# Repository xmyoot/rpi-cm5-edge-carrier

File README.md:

# CM5 Edge-Audio Carrier

A compact **Raspberry Pi Compute Module 5 carrier board** for an always-on edge-AI audio
appliance. It is designed in **KiCad 10**, impedance-controlled on a **4-layer JLCPCB stack**,
and fully routed with **0 DRC errors, 0 unconnected items and 0 schematic-parity issues**.

| | |
|---|---|
| **Compute** | Raspberry Pi CM5 (BCM2712, 4x Cortex-A76) on 2x Hirose DF40 100-pin receptacles |
| **Board** | 100 x 85 mm, 4 layers, 1.6 mm, JLC04161H-3313 stackup, ENIG |
| **Power in** | USB-C PD sink (CH224K) negotiates **12 V / 3 A**, with a TVS-clamped input |
| **Rails** | 5 V / 5 A synchronous buck (TPS565208); 3.3 V / 2 A buck for NVMe (AP3441), gated by the CM5 |
| **Storage** | M.2 Key-M socket, NVMe 2230/2242, PCIe x1 (Gen2, Gen3 capable) |
| **USB** | 1x USB 3.0 (5 Gb/s) + 1x USB 2.0 in a stacked Type-A with a 1.5 A current-limited VBUS |
| **Network** | Gigabit Ethernet RJ45 MagJack with an ESD array on every MDI pair |
| **Audio link** | 2x6 header to a 6-mic XVF3800 array: I2S + I2C control + reset/IRQ |
| **Other I/O** | USB-C service port (rpiboot / gadget), debug UART, barcode-scanner UART, Qwiic I2C, PWM fan, status LEDs, power and boot buttons |
| **Parts** | 90 footprints, 231 nets, 474 vias, 3.4 m of copper |

---

## 1. System architecture

The board started from the requirements of a Jetson Orin NX carrier for emergency-vehicle
audio. It keeps the same functional set (PD power path, NVMe, high-speed USB, GbE, I2S
mic-array link, UART/I2C management, ESD on external ports), but runs on a Raspberry Pi
CM5. Every peripheral maps to a native CM5 interface, so the carrier needs **no bridge ICs**:

| Function | CM5 interface | Carrier hardware |
|---|---|---|
| NVMe SSD | PCIe x1 (+REFCLK, PERST#, CLKREQ#, WAKE#) | M.2 Key-M socket + switched 3.3 V rail (`PCIE_PWR_EN`) |
| USB 3.0 port | USB3-0 SuperSpeed + D+/D- | Stacked Type-A (upper port), AP22653 VBUS switch |
| USB 2.0 port | USB3-1 D+/D- | Stacked Type-A (lower port) |
| Flashing / gadget | USB2 OTG | USB-C service port, USBLC6-2 ESD, 5.1k Rd |
| Ethernet | On-module BCM54210 PHY, MDI x4 | TRJG0926HENL MagJack + 2x TPD4EUSB30 |
| Mic array | PCM/I2S on GPIO18-21, I2C1, GPIO26/27 | 2x6 shrouded header, 33 ohm source termination |
| Scanner / console | UART2 / UART0 | JST-SH 4-pin / 1x3 header |

## 2. Schematic

Five hierarchical sheets ([PDF](docs/CM5_Edge_Carrier_schematic.pdf)): Root (block diagram and
notes), Power, Compute Module, High-Speed IO, and Peripheral IO.

| Power | High-speed IO |
|---|---|
|  |  |

Key circuit decisions:

* **PD with UVLO interlock.** The CH224K requests 12 V (`CFG1` = 24k). The buck's EN divider
  (100k/15k) sets the turn-on point near 9 V. If a charger can only give 5 V, the 5 V rail stays
  off instead of browning out the CM5.
* **Buck sizing.** V<sub>out</sub> = 0.76 V x (1 + 56k/10k) = 5.02 V. The worst-case load is
  CM5 3 A + USB 1.5 A + fan 0.2 A = 4.7 A, under the TPS565208's 5 A rating.
  The NVMe rail uses V<sub>out</sub> = 0.6 V x (1 + 10k/2.2k) = 3.33 V and has a 4.7 nF feed-forward cap.
* **The NVMe rail is gated by the SoC** (`PCIE_PWR_EN` with a 100k pull-down). The SSD stays
  unpowered until the bootloader wants it, as on the Raspberry Pi reference design.
* **The ESD strategy follows the threat.** SMAJ15A on the PD input, TPD4EUSB30 on all four GbE
  pairs, and USBLC6-2 on the service port. The USB-A ports follow the Raspberry Pi CM5 IO
  reference, which has no array on the 5 Gb/s pair, so that pair stays stub- and via-free.

## 3. PCB layout

| Top copper | Bottom copper |
|---|---|
|  |  |

**Floorplan.** The CM5 is rotated so its high-speed connector (PCIe/USB) faces the front edge.
The USB 3.0 jack, the service USB-C and the M.2 socket sit directly at those pins. The Ethernet
pins face the rear edge, where the MagJack is. Power enters at the top-left and the M.2 buck
sits next to the socket. Nothing is placed under the module.

**Stackup and impedance.** JLC04161H-3313: L1 signal / **L2 solid GND** / L3 power (+5 V plane
with a +3V3_M2 island) / L4 signal. The widths below were solved with the
[KiCadRoutingTools](https://github.com/drandyhaas/KiCadRoutingTools) microstrip models for L1
over 0.0994 mm 3313 prepreg (εr 4.1):

| Class | Target | Width / gap | Calculated |
|---|---|---|---|
| PCIe TX/RX/REFCLK | 85 ohm diff | 0.20 / 0.15 mm | 85.6 ohm |
| USB 3.0 SS, USB 2.0 | 90 ohm diff | 0.18 / 0.15 mm | 90.8 ohm |
| 1000BASE-T MDI | 100 ohm diff | 0.16 / 0.18 mm | 100.0 ohm |

**High-speed results**, measured from the routed copper by `scripts/si_report.py`:

| Pair | Length P / N (mm) | Intra-pair skew | Vias | Layer |
|---|---|---|---|---|
| PCIe TX | 52.33 / 52.33 | 0.01 mm | 0 | L1 only |
| PCIe RX | 99.69 / 99.69 | 0.00 mm | 0 | L1 only |
| PCIe REFCLK | 50.02 / 49.76 | 0.26 mm | 4 | L1/L4 (must cross TX/RX) |
| USB 3.0 SSTX | 11.37 / 11.33 | 0.04 mm | 0 | L1 only |
| USB 3.0 SSRX | 9.20 / 9.20 | 0.00 mm | 0 | L1 only |
| USB-A1 D+/D- | 10.66 / 11.24 | 0.58 mm | 0 | L1 only |
| USB-A2 D+/D- | 55.01 / 55.07 | 0.06 mm | 4 | L1/L4 |

The 5 Gb/s and PCIe data pairs stay on L1, over an unbroken L2 ground, with no layer changes,
and their P/N lengths are matched with meanders. The Ethernet pairs carry short T-stubs to their
ESD clamps. At 125 MBd those stubs are electrically negligible.

**Power stage.** Both bucks are laid out by hand on top-layer copper pours: input cap, then IC,
then inductor, then output caps, in a tight loop with stitched returns. The CM5's 0.4 mm-pitch
DF40 pads use a custom staggered escape fanout (0.4/0.2 mm vias, 3 levels) that keeps the
design on JLC's standard process. Outer GND pours are stitched to L2 on a 4 mm grid
(about 210 vias).

| Rear (RJ45, mic header) | Top |
|---|---|
|  |  |

## 4. Engineering trade-offs (documented, deliberate)

1. **CM5 instead of Jetson Orin NX.** The same functions at a fraction of the power and cost. NVMe
   runs at PCIe Gen2/3 x1 instead of Gen3 x4.
2. **Lower USB-A port is USB 2.0.** The far contact row of a stacked USB3 jack is only reachable
   by threading pairs between the near-row pins. One clean 5 Gb/s port covers the 5G-modem use
   case, so the CM5's second SuperSpeed lane is left unconnected.
3. **No battery charger.** The input path is PD to buck. A UPS or battery stage would be a
   daughterboard.
4. **The CM5 CC1/CC2 pins are left open.** PD is negotiated by the CH224K, so set
   `usb_max_current_enable=1` in `config.txt` to get full USB current.
5. **LCSC codes** are filled in where verified against the LCSC catalogue (October 2026). The
   remaining lines are ordered by manufacturer part number.

## 5. Fabrication package (`fab/`)

* `CM5_Edge_Carrier_gerbers.zip`: Gerber X2 for 4 copper layers, mask, paste, silk, outline, and Excellon drills
* `CM5_Edge_Carrier_BOM_JLC.csv` / `CM5_Edge_Carrier_CPL_JLC.csv`: JLCPCB SMT assembly format
* `CM5_Edge_Carrier.step`: full 3D assembly, including the CM5 module
* `CM5_Edge_Carrier_schematic.pdf`, `CM5_Edge_Carrier_top_assembly.pdf`

Order notes: JLC04161H-3313 impedance control, 1.6 mm, ENIG, minimum via 0.4/0.2 mm, and
minimum track/space 0.1/0.1 mm. Everything is on JLC's standard multilayer tier.

## 6. Reproducible design flow (`scripts/`)

The schematic, board, routing and fab outputs are generated from one design database, so
they cannot drift apart:

```
design.py          parts, values, nets, schematic placement     (single source of truth)
gen_sch.py         -> hierarchical KiCad schematic with wires, labels and frames
check_netlist.py   KiCad-exported netlist == design.py           (catches any wiring error)
gen_pcb.py         -> board: floorplan, stackup, netclasses, power-stage pours
fanout_cm5.py      staggered DF40 escape vias
route_chain.sh     KiCadRoutingTools: diff pairs (85/90/100 ohm, length-matched) -> general routing
finish_pcb.py / stitch_gnd.py / silk_cleanup.py   zone fill, GND stitching, silkscreen placement
si_report.py       length / skew / via report
make_outputs.sh    Gerbers, drills, JLC BOM/CPL, STEP, PDFs, renders
```

`scripts/build_all.sh` runs the whole flow, from schematic to a DRC-clean routed board, in
about 4 minutes. Requirements: KiCad 10 (its bundled Python runs the `pcbnew` scripts; the
paths are set at the top of each shell script), plus
`git clone https://github.com/drandyhaas/KiCadRoutingTools ref/KiCadRoutingTools` followed by
`python3 ref/KiCadRoutingTools/build_router.py`.

## 7. Repository layout

```
hardware/   KiCad 10 project (schematic, PCB, project rules, project symbol/footprint/3D library)
fab/        manufacturing outputs
docs/       renders, layer plots, schematic PDF
scripts/    generators and build flow
```

## Credits and licenses

* The CM5 symbol, DF40 footprint, magjack, stacked USB3 and M.2 footprints and their 3D models
  are adapted from the **Raspberry Pi CM5 IO Board** KiCad design files (Raspberry Pi Ltd,
  [design-files licence](https://pip.raspberrypi.com)). The CM5 STEP model is © Raspberry Pi Ltd.
* Approach inspired by Shawn Hymel's
  [CM4 carrier template](https://github.com/ShawnHymel/rpi-cm4-carrier-template) and the
  [MakerForge CM5 carrier basics](https://www.makerforge.tech/posts/cm5-carrier-basics/).
* Routing by [KiCadRoutingTools](https://github.com/drandyhaas/KiCadRoutingTools) (MIT).
  Design review by [kicad-happy](https://github.com/aklofas/kicad-happy).
* This design: hardware files are CC BY 4.0, scripts are MIT. Hector Jimenez, 2026.

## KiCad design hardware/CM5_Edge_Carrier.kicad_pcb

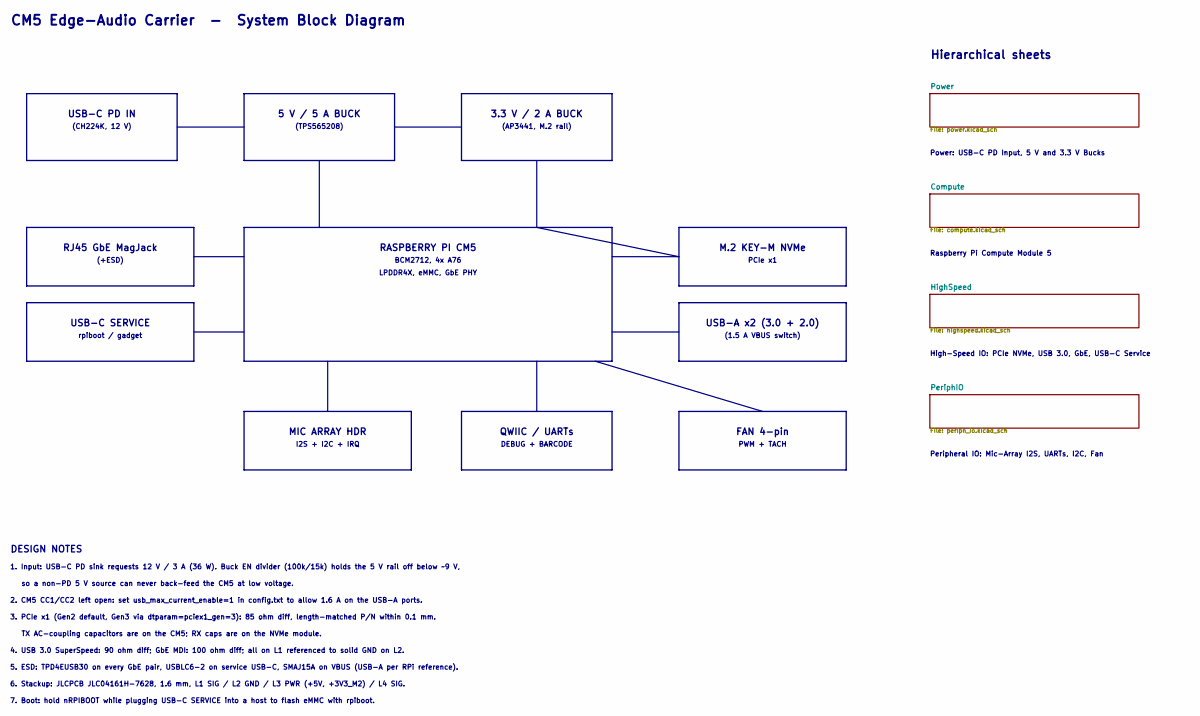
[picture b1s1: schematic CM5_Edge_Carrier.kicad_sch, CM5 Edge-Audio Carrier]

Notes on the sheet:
USB-C PD IN
(CH224K, 12 V)
5 V / 5 A BUCK
(TPS565208)
3.3 V / 2 A BUCK
(AP3441, M.2 rail)
RASPBERRY PI CM5
BCM2712, 4x A76
LPDDR4X, eMMC, GbE PHY
M.2 KEY-M NVMe
PCIe x1
USB-A x2 (3.0 + 2.0)
(1.5 A VBUS switch)
RJ45 GbE MagJack
(+ESD)
USB-C SERVICE
rpiboot / gadget
MIC ARRAY HDR
I2S + I2C + IRQ
QWIIC / UARTs
DEBUG + BARCODE
FAN 4-pin
PWM + TACH
CM5 Edge-Audio Carrier - System Block Diagram
DESIGN NOTES
1. Input: USB-C PD sink requests 12 V / 3 A (36 W). Buck EN divider (100k/15k) holds the 5 V rail off below ~9 V,
so a non-PD 5 V source can never back-feed the CM5 at low voltage.
2. CM5 CC1/CC2 left open: set usb_max_current_enable=1 in config.txt to allow 1.6 A on the USB-A ports.
3. PCIe x1 (Gen2 default, Gen3 via dtparam=pciex1_gen=3): 85 ohm diff, length-matched P/N within 0.1 mm.
TX AC-coupling capacitors are on the CM5; RX caps are on the NVMe module.
4. USB 3.0 SuperSpeed: 90 ohm diff; GbE MDI: 100 ohm diff; all on L1 referenced to solid GND on L2.
5. ESD: TPD4EUSB30 on every GbE pair, USBLC6-2 on service USB-C, SMAJ15A on VBUS (USB-A per RPi reference).
6. Stackup: JLCPCB JLC04161H-7628, 1.6 mm, L1 SIG / L2 GND / L3 PWR (+5V, +3V3_M2) / L4 SIG.
7. Boot: hold nRPIBOOT while plugging USB-C SERVICE into a host to flash eMMC with rpiboot.
Hierarchical sheets
Power: USB-C PD Input, 5 V and 3.3 V Bucks
Raspberry Pi Compute Module 5
High-Speed IO: PCIe NVMe, USB 3.0, GbE, USB-C Service
Peripheral IO: Mic-Array I2S, UARTs, I2C, Fan

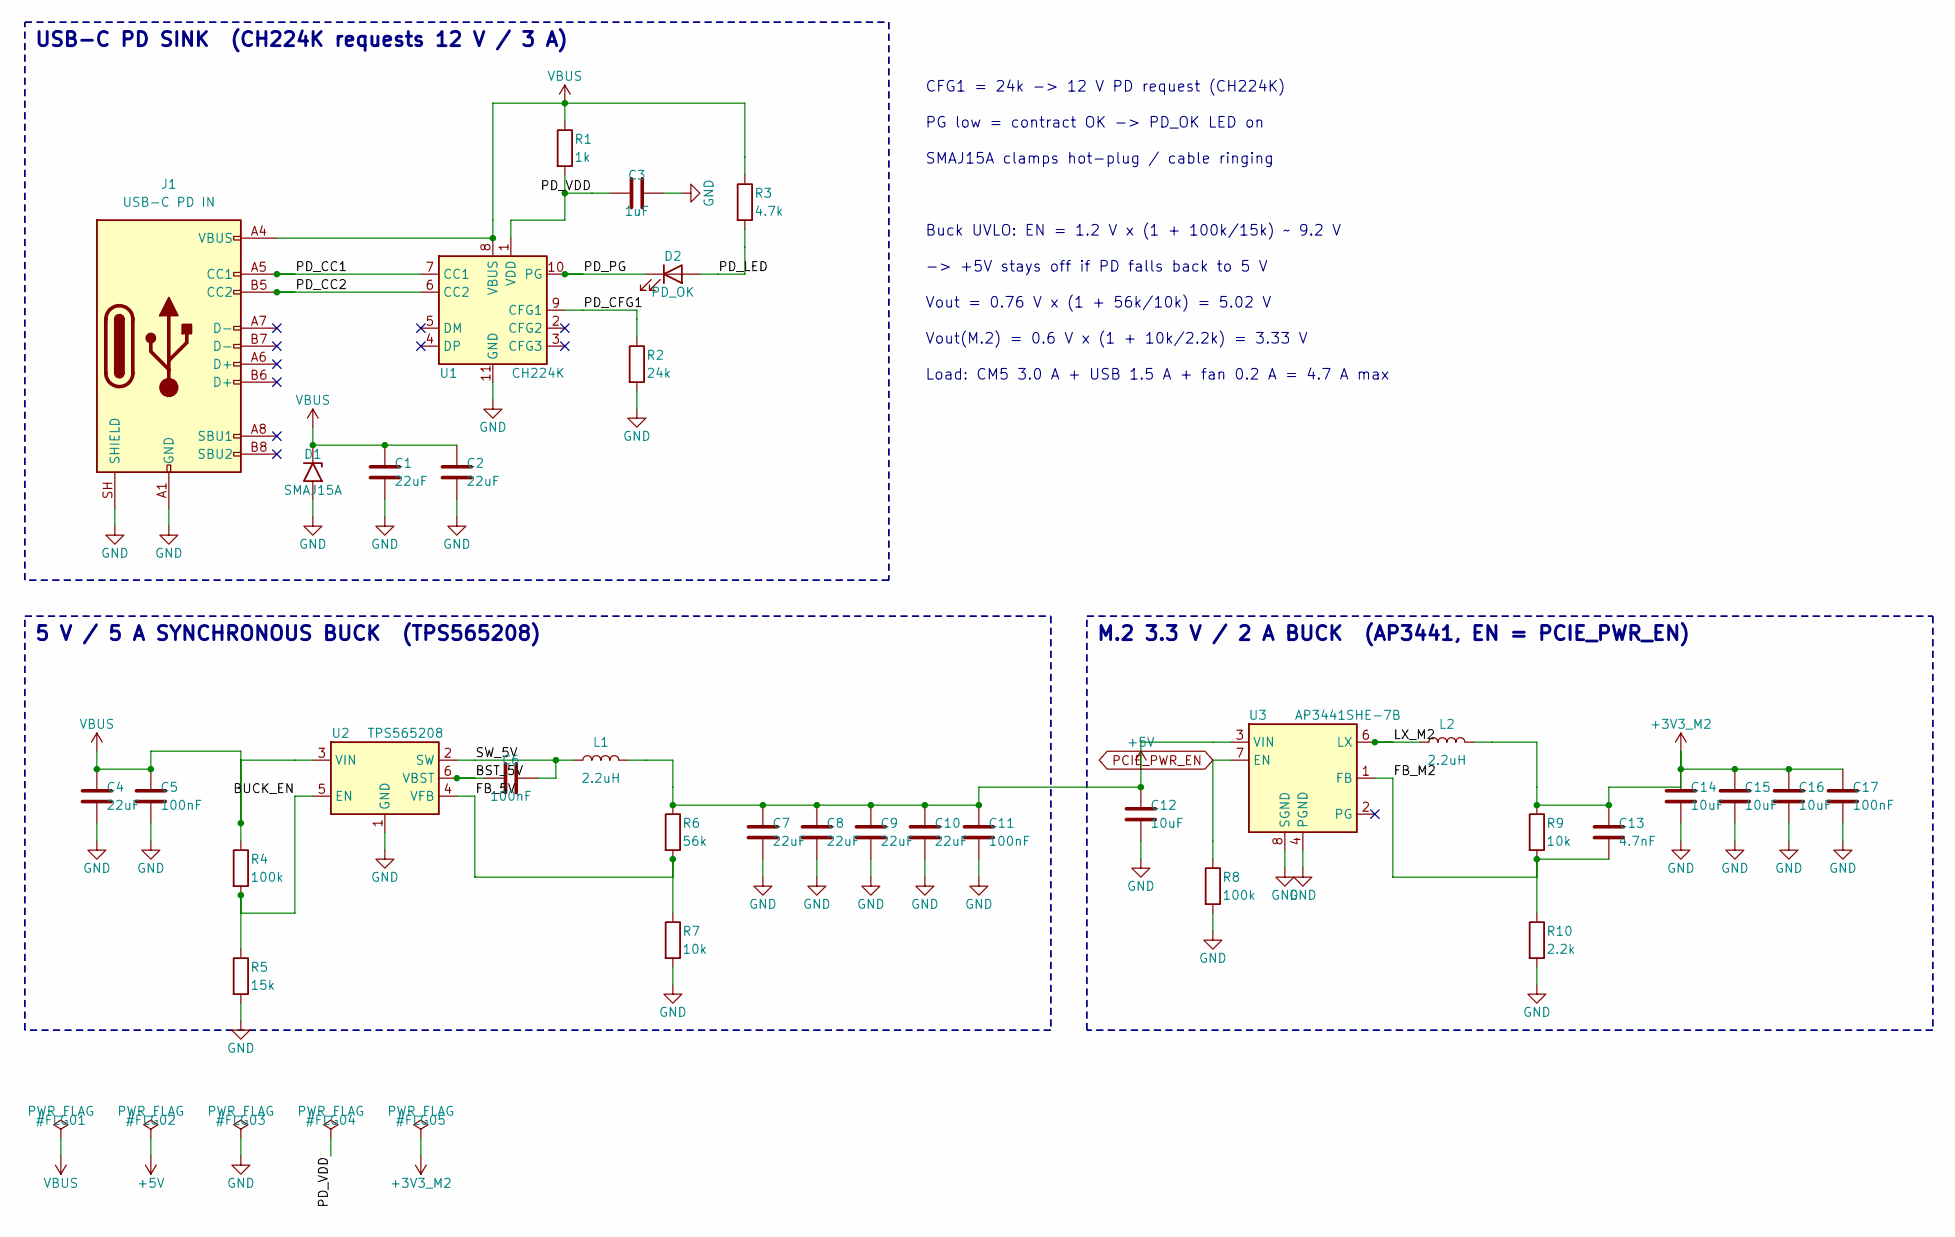
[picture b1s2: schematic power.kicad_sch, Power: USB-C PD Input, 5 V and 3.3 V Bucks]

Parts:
C1, C2, C4: 22uF; C_1206_3216Metric; Voltage 25V; LCSC C12891
C3: 1uF; C_0402_1005Metric; Voltage 16V; LCSC C52923
C5, C6, C11, C17: 100nF; C_0402_1005Metric; Voltage 16V; LCSC C1525
C7, C8, C9, C10: 22uF; C_0805_2012Metric; Voltage 10V; LCSC C45783
C12, C14, C15, C16: 10uF; C_0805_2012Metric; Voltage 10V; LCSC C15850
C13: 4.7nF; C_0402_1005Metric; Voltage 16V; LCSC C1538
D1: SMAJ15A; D_SMA; MPN Littelfuse SMAJ15A
D2: PD_OK; LED_0603_1608Metric; LCSC C72043
J1: USB-C PD IN; USB_C_Receptacle_GCT_USB4105-xx-A_16P_TopMnt_Horizontal; MPN GCT USB4105-GF-A; LCSC C3020560
L1: 2.2uH; L_Sunlord_MWSA0603S; Rating 2.2uH 10A; MPN Sunlord MWSA0603S-2R2MT
L2: 2.2uH; L_Bourns_SRP5030T; Rating 2.2uH 6.5A; MPN Bourns SRP5030T-2R2M
R1: 1k; R_0402_1005Metric; Tolerance 1%; LCSC C11702
R2: 24k; R_0402_1005Metric; Tolerance 1%
R3: 4.7k; R_0402_1005Metric; Tolerance 1%; LCSC C25900
R4, R8: 100k; R_0402_1005Metric; Tolerance 1%; LCSC C25741
R5: 15k; R_0402_1005Metric; Tolerance 1%; LCSC C25756
R6: 56k; R_0402_1005Metric; Tolerance 1%; LCSC C25796
R7, R9: 10k; R_0402_1005Metric; Tolerance 1%; LCSC C25744
R10: 2.2k; R_0402_1005Metric; Tolerance 1%; LCSC C25879
U1: CH224K; SSOP-10-1EP_3.9x4.9mm_P1mm_EP2.1x3.3mm; MPN WCH CH224K; LCSC C970725
U2: TPS565208; SOT-23-6; MPN TI TPS565208DDCR
U3: AP3441SHE-7B; DFN-8-1EP_2x2mm_P0.5mm_EP0.9x1.7mm; MPN Diodes AP3441SHE-7B

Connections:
+3V3_M2: C13.1, C14.1, C15.1, C16.1, C17.1, L2.2, R9.1; also elsewhere on the board
+5V: C7.1, C8.1, C9.1, C10.1, C11.1, C12.1, L1.2, R6.1, U3.3 (VIN); also elsewhere on the board
/Power/BST_5V: C6.1, U2.6 (VBST)
/Power/BUCK_EN: R4.2, R5.1, U2.5 (EN)
/Power/FB_5V: R6.2, R7.1, U2.4 (VFB)
/Power/FB_M2: C13.2, R9.2, R10.1, U3.1 (FB)
/Power/LX_M2: L2.1, U3.6 (LX)
/Power/PD_CC1: J1.A5 (CC1), U1.7 (CC1)
/Power/PD_CC2: J1.B5 (CC2), U1.6 (CC2)
/Power/PD_CFG1: R2.1, U1.9 (CFG1)
/Power/PD_LED: D2.2 (A), R3.2
/Power/PD_PG: D2.1 (K), U1.10 (PG)
/Power/PD_VDD: C3.1, R1.2, U1.1 (VDD)
/Power/SW_5V: C6.2, L1.1, U2.2 (SW)
GND: C1.2, C2.2, C3.2, C4.2, C5.2, C7.2, C8.2, C9.2, C10.2, C11.2, C12.2, C14.2, C15.2, C16.2, C17.2, D1.2 (A2), J1.A1 (GND), J1.A12 (GND), J1.B1 (GND), J1.B12 (GND), J1.SH (SHIELD), R2.2, R5.2, R7.2, R8.2, R10.2, U1.11 (GND), U2.1 (GND), U3.4 (PGND), U3.8 (SGND), U3.9 (SGND); also elsewhere on the board
PCIE_PWR_EN: R8.1, U3.7 (EN); also elsewhere on the board
VBUS: C1.1, C2.1, C4.1, C5.1, D1.1 (A1), J1.A4 (VBUS), J1.A9 (VBUS), J1.B4 (VBUS), J1.B9 (VBUS), R1.1, R3.1, R4.1, U1.8 (VBUS), U2.3 (VIN)

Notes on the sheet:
USB-C PD SINK (CH224K requests 12 V / 3 A)
5 V / 5 A SYNCHRONOUS BUCK (TPS565208)
M.2 3.3 V / 2 A BUCK (AP3441, EN = PCIE_PWR_EN)
CFG1 = 24k -> 12 V PD request (CH224K)
PG low = contract OK -> PD_OK LED on
SMAJ15A clamps hot-plug / cable ringing
Buck UVLO: EN = 1.2 V x (1 + 100k/15k) ~ 9.2 V
-> +5V stays off if PD falls back to 5 V
Vout = 0.76 V x (1 + 56k/10k) = 5.02 V
Vout(M.2) = 0.6 V x (1 + 10k/2.2k) = 3.33 V
Load: CM5 3.0 A + USB 1.5 A + fan 0.2 A = 4.7 A max

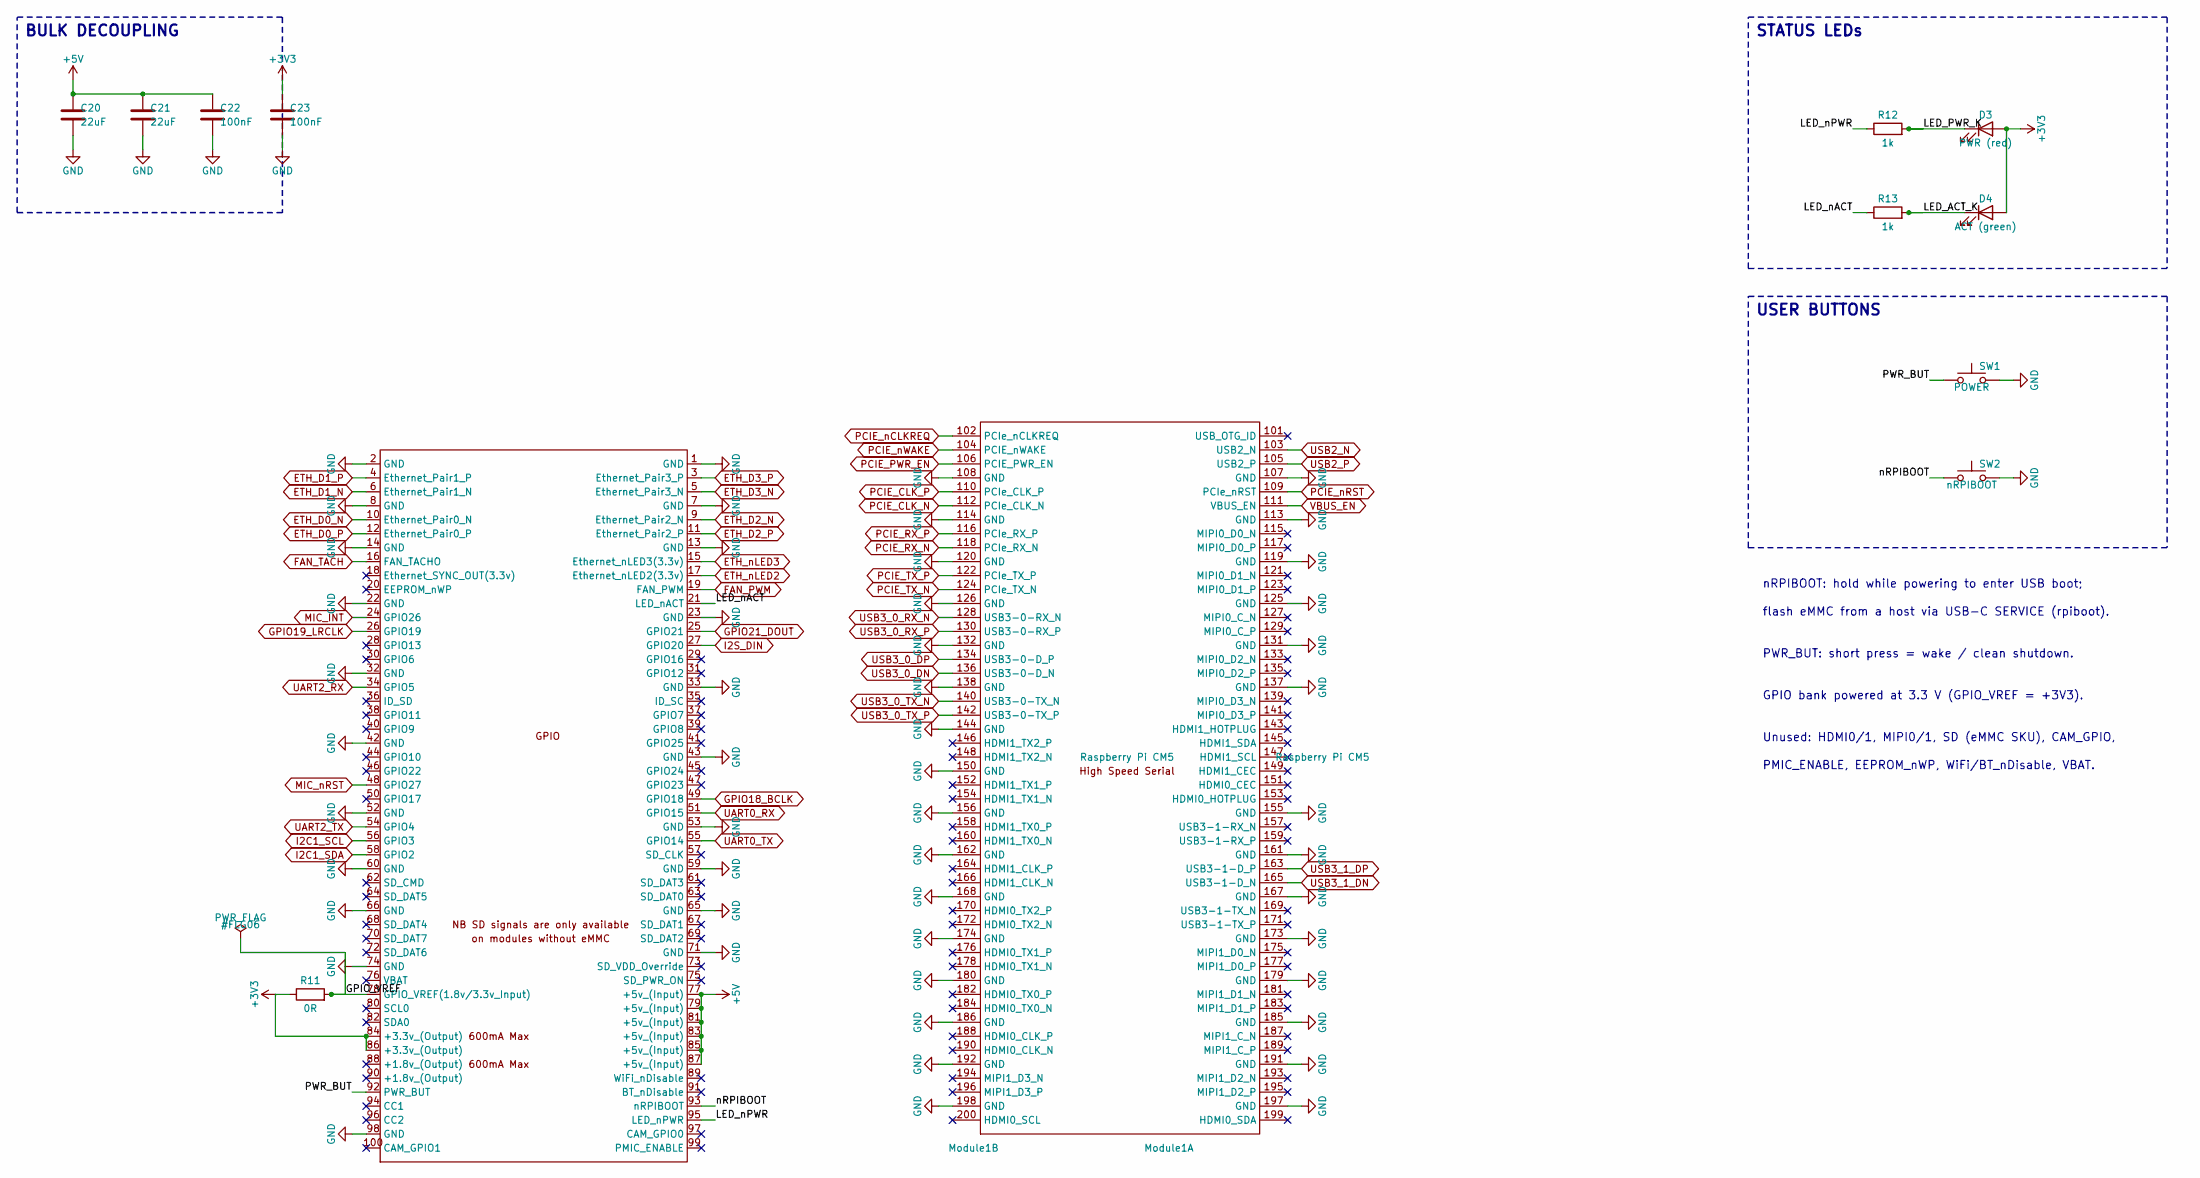
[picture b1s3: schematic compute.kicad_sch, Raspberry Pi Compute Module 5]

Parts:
C20, C21: 22uF; C_0805_2012Metric; Voltage 10V; LCSC C45783
C22, C23: 100nF; C_0402_1005Metric; Voltage 16V; LCSC C1525
D3: PWR (red); LED_0603_1608Metric; LCSC C2286
D4: ACT (green); LED_0603_1608Metric; LCSC C72043
Module1: Raspberry Pi CM5; RPi_CM5_DF40; MPN Raspberry Pi CM5 + 2x Hirose DF40C-100D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; LCSC C597931 (x2)
R11: 0R; R_0402_1005Metric; Tolerance 1%; LCSC C17168
R12, R13: 1k; R_0402_1005Metric; Tolerance 1%; LCSC C11702
SW1: POWER; SW_SPST_B3U-1000P; MPN Omron B3U-1000P; LCSC C231329
SW2: nRPIBOOT; SW_SPST_B3U-1000P; MPN Omron B3U-1000P; LCSC C231329

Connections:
+3V3: C23.1, D3.2 (A), D4.2 (A), Module1.84 (+3.3v_(Output)), Module1.86 (+3.3v_(Output)), R11.1; also elsewhere on the board
+5V: C20.1, C21.1, C22.1, Module1.77 (+5v_(Input)), Module1.79 (+5v_(Input)), Module1.81 (+5v_(Input)), Module1.83 (+5v_(Input)), Module1.85 (+5v_(Input)), Module1.87 (+5v_(Input)); also elsewhere on the board
/Compute/GPIO_VREF: Module1.78 (GPIO_VREF(1.8v/3.3v_Input)), R11.2
/Compute/LED_ACT_K: D4.1 (K), R13.2
/Compute/LED_PWR_K: D3.1 (K), R12.2
/Compute/LED_nACT: Module1.21 (LED_nACT), R13.1
/Compute/LED_nPWR: Module1.95 (LED_nPWR), R12.1
/Compute/PWR_BUT: Module1.92 (PWR_BUT), SW1.1
/Compute/nRPIBOOT: Module1.93 (nRPIBOOT), SW2.1
ETH_D0_N: Module1.10 (Ethernet_Pair0_N); also elsewhere on the board
ETH_D0_P: Module1.12 (Ethernet_Pair0_P); also elsewhere on the board
ETH_D1_N: Module1.6 (Ethernet_Pair1_N); also elsewhere on the board
ETH_D1_P: Module1.4 (Ethernet_Pair1_P); also elsewhere on the board
ETH_D2_N: Module1.9 (Ethernet_Pair2_N); also elsewhere on the board
ETH_D2_P: Module1.11 (Ethernet_Pair2_P); also elsewhere on the board
ETH_D3_N: Module1.5 (Ethernet_Pair3_N); also elsewhere on the board
ETH_D3_P: Module1.3 (Ethernet_Pair3_P); also elsewhere on the board
ETH_nLED2: Module1.17 (Ethernet_nLED2(3.3v)); also elsewhere on the board
ETH_nLED3: Module1.15 (Ethernet_nLED3(3.3v)); also elsewhere on the board
FAN_PWM: Module1.19 (FAN_PWM); also elsewhere on the board
FAN_TACH: Module1.16 (FAN_TACHO); also elsewhere on the board
GND: C20.2, C21.2, C22.2, C23.2, Module1.1 (GND), Module1.2 (GND), Module1.7 (GND), Module1.8 (GND), Module1.13 (GND), Module1.14 (GND), Module1.22 (GND), Module1.23 (GND), Module1.32 (GND), Module1.33 (GND), Module1.42 (GND), Module1.43 (GND), Module1.52 (GND), Module1.53 (GND), Module1.59 (GND), Module1.60 (GND), Module1.65 (GND), Module1.66 (GND), Module1.71 (GND), Module1.74 (GND), Module1.98 (GND), Module1.107 (GND), Module1.108 (GND), Module1.113 (GND), Module1.114 (GND), Module1.119 (GND), Module1.120 (GND), Module1.125 (GND), Module1.126 (GND), Module1.131 (GND), Module1.132 (GND), Module1.137 (GND), Module1.138 (GND), Module1.144 (GND), Module1.150 (GND), Module1.155 (GND), Module1.156 (GND), Module1.161 (GND), Module1.162 (GND), Module1.167 (GND), Module1.168 (GND), Module1.173 (GND), Module1.174 (GND), Module1.179 (GND), Module1.180 (GND), Module1.185 (GND), Module1.186 (GND), Module1.191 (GND), Module1.192 (GND), Module1.197 (GND), Module1.198 (GND), SW1.2, SW2.2; also elsewhere on the board
GPIO18_BCLK: Module1.49 (GPIO18); also elsewhere on the board
GPIO19_LRCLK: Module1.26 (GPIO19); also elsewhere on the board
GPIO21_DOUT: Module1.25 (GPIO21); also elsewhere on the board
I2C1_SCL: Module1.56 (GPIO3); also elsewhere on the board
I2C1_SDA: Module1.58 (GPIO2); also elsewhere on the board
I2S_DIN: Module1.27 (GPIO20); also elsewhere on the board
MIC_INT: Module1.24 (GPIO26); also elsewhere on the board
MIC_nRST: Module1.48 (GPIO27); also elsewhere on the board
PCIE_CLK_N: Module1.112 (PCIe_CLK_N); also elsewhere on the board
PCIE_CLK_P: Module1.110 (PCIe_CLK_P); also elsewhere on the board
PCIE_PWR_EN: Module1.106 (PCIE_PWR_EN); also elsewhere on the board
PCIE_RX_N: Module1.118 (PCIe_RX_N); also elsewhere on the board
PCIE_RX_P: Module1.116 (PCIe_RX_P); also elsewhere on the board
PCIE_TX_N: Module1.124 (PCIe_TX_N); also elsewhere on the board
PCIE_TX_P: Module1.122 (PCIe_TX_P); also elsewhere on the board
PCIE_nCLKREQ: Module1.102 (PCIe_nCLKREQ); also elsewhere on the board
PCIE_nRST: Module1.109 (PCIe_nRST); also elsewhere on the board
PCIE_nWAKE: Module1.104 (PCIE_nWAKE); also elsewhere on the board
UART0_RX: Module1.51 (GPIO15); also elsewhere on the board
UART0_TX: Module1.55 (GPIO14); also elsewhere on the board
UART2_RX: Module1.34 (GPIO5); also elsewhere on the board
UART2_TX: Module1.54 (GPIO4); also elsewhere on the board
USB2_N: Module1.103 (USB2_N); also elsewhere on the board
USB2_P: Module1.105 (USB2_P); also elsewhere on the board
USB3_0_DN: Module1.136 (USB3-0-D_N); also elsewhere on the board
USB3_0_DP: Module1.134 (USB3-0-D_P); also elsewhere on the board
USB3_0_RX_N: Module1.128 (USB3-0-RX_N); also elsewhere on the board
USB3_0_RX_P: Module1.130 (USB3-0-RX_P); also elsewhere on the board
USB3_0_TX_N: Module1.140 (USB3-0-TX_N); also elsewhere on the board
USB3_0_TX_P: Module1.142 (USB3-0-TX_P); also elsewhere on the board
USB3_1_DN: Module1.165 (USB3-1-D_N); also elsewhere on the board
USB3_1_DP: Module1.163 (USB3-1-D_P); also elsewhere on the board
VBUS_EN: Module1.111 (VBUS_EN); also elsewhere on the board

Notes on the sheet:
BULK DECOUPLING
STATUS LEDs
USER BUTTONS
nRPIBOOT: hold while powering to enter USB boot;
flash eMMC from a host via USB-C SERVICE (rpiboot).
PWR_BUT: short press = wake / clean shutdown.
GPIO bank powered at 3.3 V (GPIO_VREF = +3V3).
Unused: HDMI0/1, MIPI0/1, SD (eMMC SKU), CAM_GPIO,
PMIC_ENABLE, EEPROM_nWP, WiFi/BT_nDisable, VBAT.

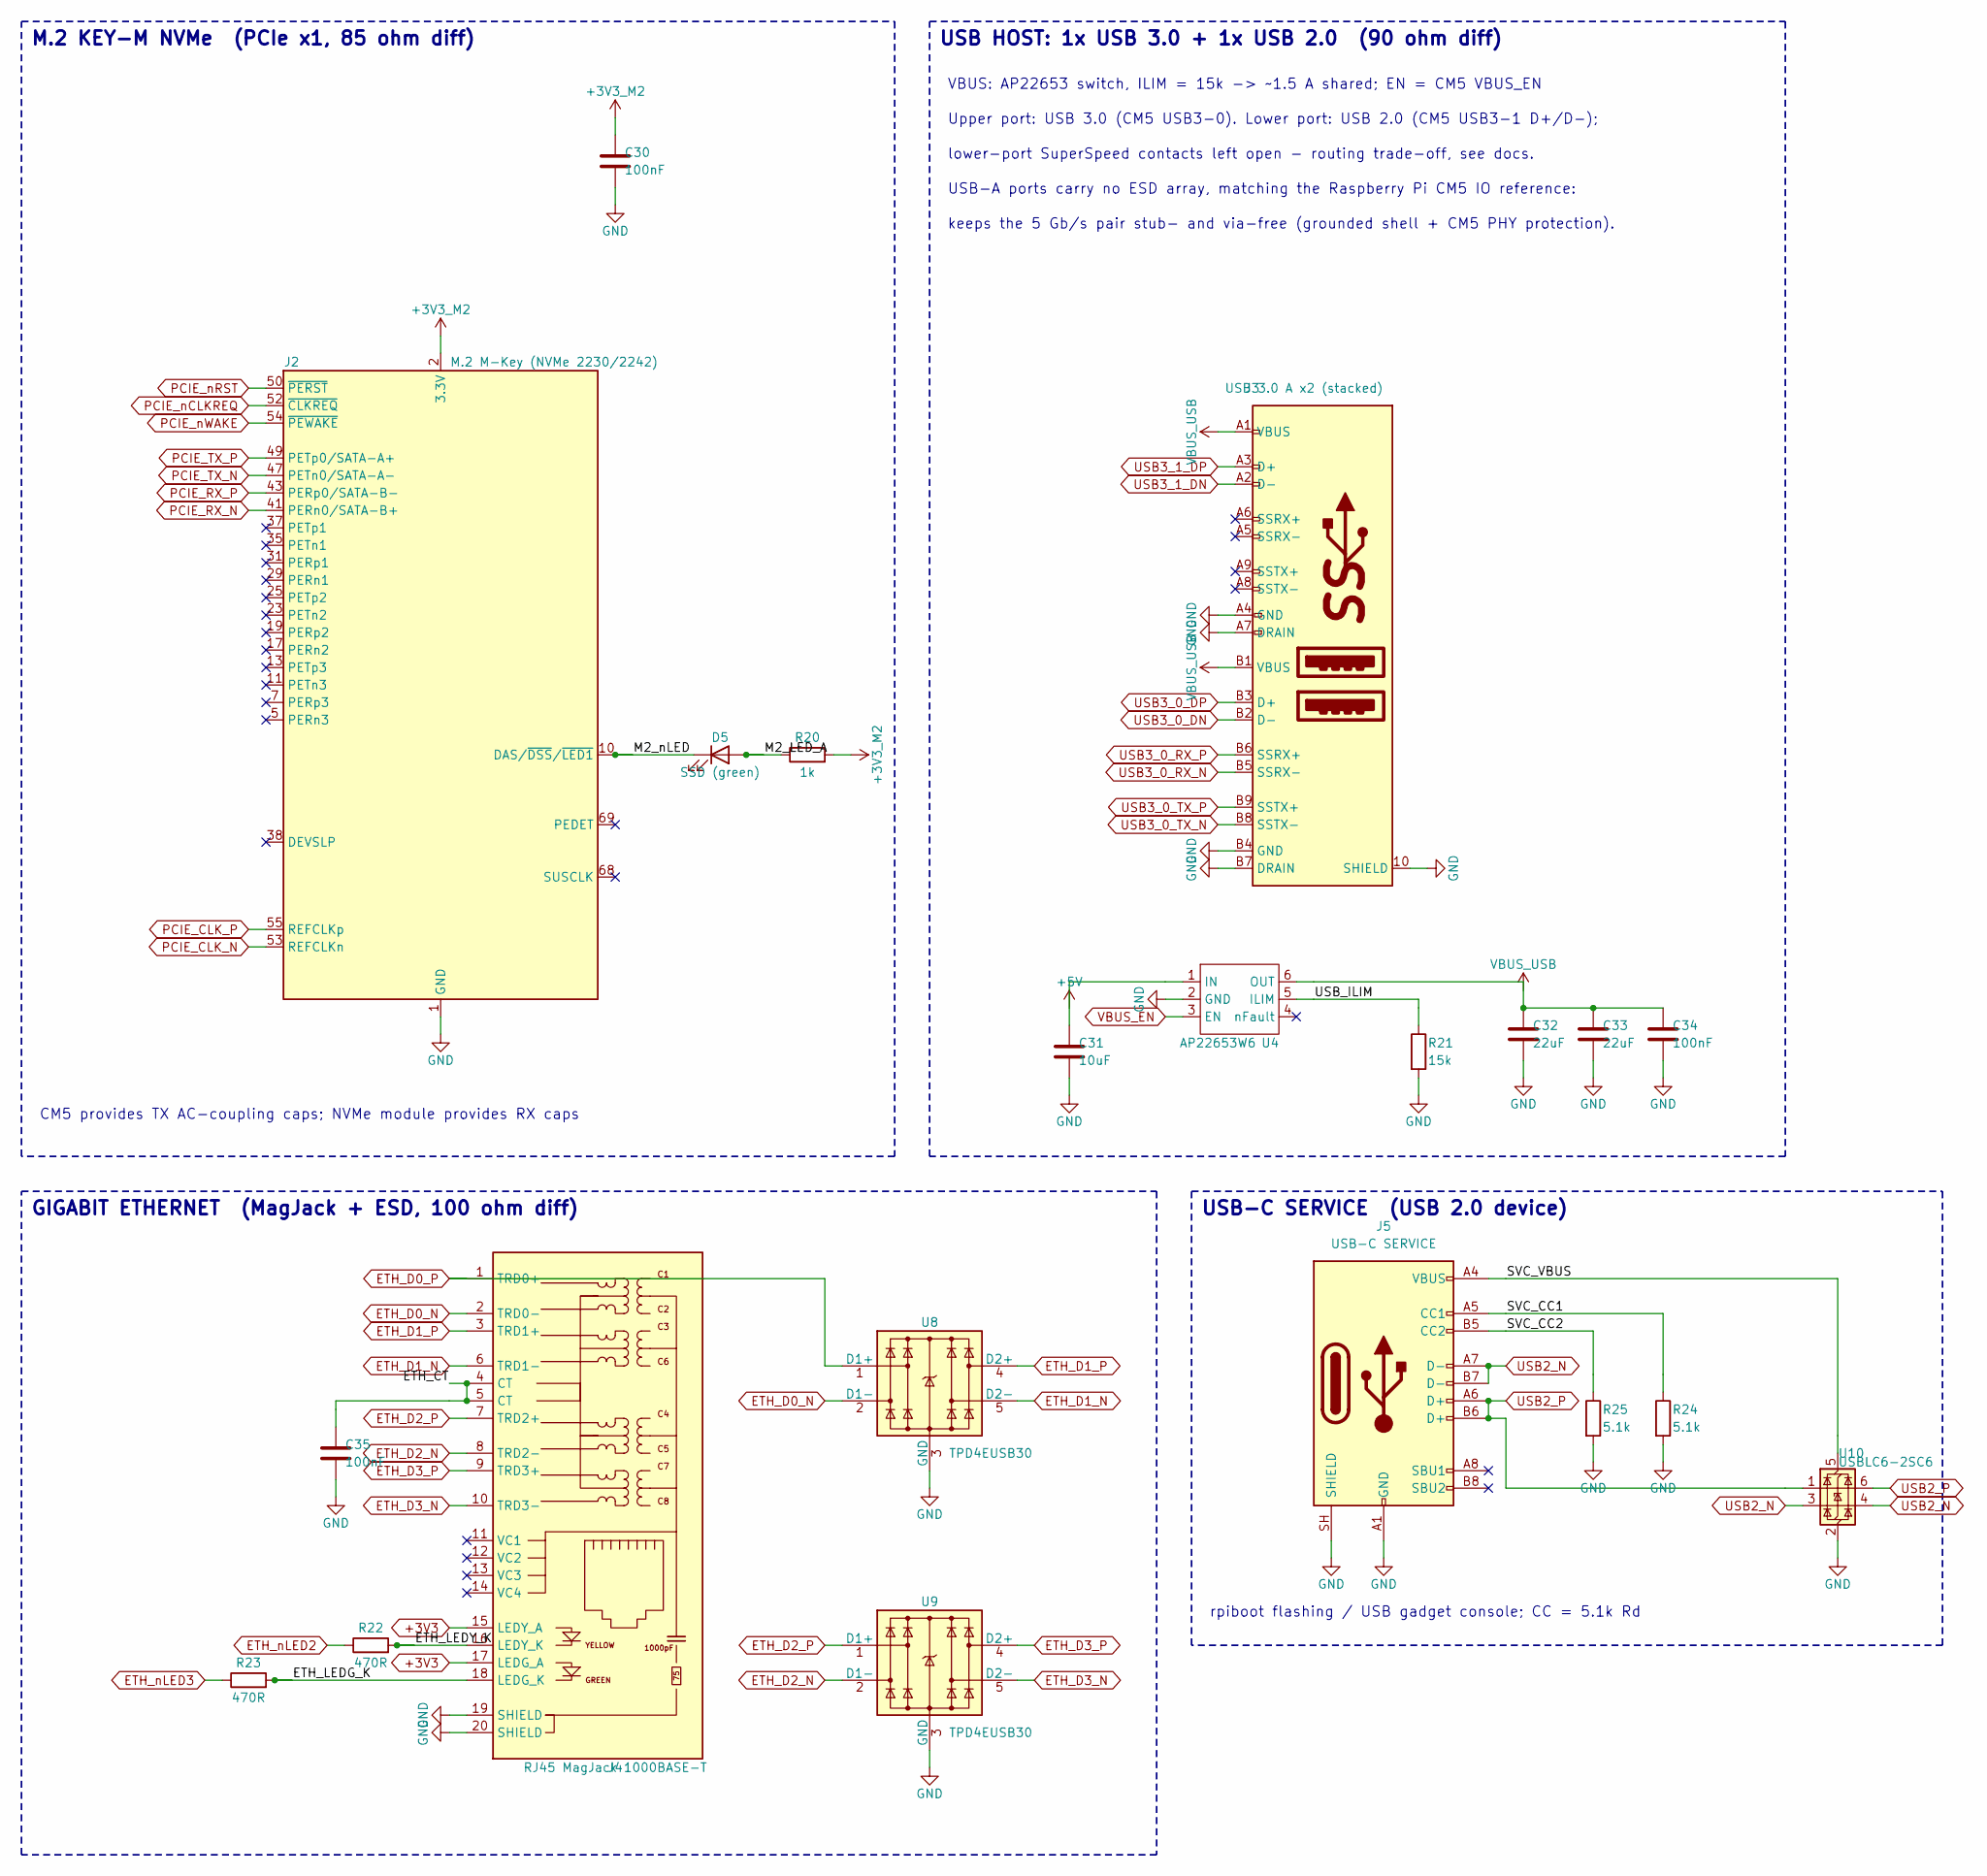
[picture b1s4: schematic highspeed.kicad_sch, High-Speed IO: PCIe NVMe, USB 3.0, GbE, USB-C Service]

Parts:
C30, C34, C35: 100nF; C_0402_1005Metric; Voltage 16V; LCSC C1525
C31: 10uF; C_0805_2012Metric; Voltage 10V; LCSC C15850
C32, C33: 22uF; C_0805_2012Metric; Voltage 10V; LCSC C45783
D5: SSD (green); LED_0603_1608Metric; LCSC C72043
J2: M.2 M-Key (NVMe 2230/2242); M.2_M_Key_2242; MPN MTCONN MTSSD03-67MSW337 (H=3.2 mm)
J3: USB 3.0 A x2 (stacked); MTCONN_UBAF30-D2011; MPN MTCONN UBAF30-D2011
J4: RJ45 MagJack 1000BASE-T; TRJG0926HENL; MPN Trxcom TRJG0926HENL
J5: USB-C SERVICE; USB_C_Receptacle_GCT_USB4105-xx-A_16P_TopMnt_Horizontal; MPN GCT USB4105-GF-A; LCSC C3020560
R20: 1k; R_0402_1005Metric; Tolerance 1%; LCSC C11702
R21: 15k; R_0402_1005Metric; Tolerance 1%; LCSC C25756
R22, R23: 470R; R_0402_1005Metric; Tolerance 1%; LCSC C25117
R24, R25: 5.1k; R_0402_1005Metric; Tolerance 1%; LCSC C25905
U4: AP22653W6; SOT-23-6; MPN Diodes AP22653W6-7
U8, U9: TPD4EUSB30; USON-10_2.5x1.0mm_P0.5mm; MPN TI TPD4EUSB30DQAR
U10: USBLC6-2SC6; SOT-23-6; MPN ST USBLC6-2SC6; LCSC C7519

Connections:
+3V3: J4.15 (LEDY_A), J4.17 (LEDG_A); also elsewhere on the board
+3V3_M2: C30.1, J2.2 (3.3V), J2.4 (3.3V), J2.12 (3.3V), J2.14 (3.3V), J2.16 (3.3V), J2.18 (3.3V), J2.70 (3.3V), J2.72 (3.3V), J2.74 (3.3V), R20.2; also elsewhere on the board
+5V: C31.1, U4.1 (IN); also elsewhere on the board
/HighSpeed/ETH_CT: C35.1, J4.4 (CT), J4.5 (CT)
/HighSpeed/ETH_LEDG_K: J4.18 (LEDG_K), R23.2
/HighSpeed/ETH_LEDY_K: J4.16 (LEDY_K), R22.2
/HighSpeed/M2_LED_A: D5.2 (A), R20.1
/HighSpeed/M2_nLED: D5.1 (K), J2.10 (DAS/~DSS/~LED1)
/HighSpeed/SVC_CC1: J5.A5 (CC1), R24.1
/HighSpeed/SVC_CC2: J5.B5 (CC2), R25.1
/HighSpeed/SVC_VBUS: J5.A4 (VBUS), J5.A9 (VBUS), J5.B4 (VBUS), J5.B9 (VBUS), U10.5 (VBUS)
/HighSpeed/USB_ILIM: R21.1, U4.5 (ILIM)
ETH_D0_N: J4.2 (TRD0-), U8.2 (D1-), U8.9; also elsewhere on the board
ETH_D0_P: J4.1 (TRD0+), U8.1 (D1+), U8.10; also elsewhere on the board
ETH_D1_N: J4.6 (TRD1-), U8.5 (D2-), U8.6; also elsewhere on the board
ETH_D1_P: J4.3 (TRD1+), U8.4 (D2+), U8.7; also elsewhere on the board
ETH_D2_N: J4.8 (TRD2-), U9.2 (D1-), U9.9; also elsewhere on the board
ETH_D2_P: J4.7 (TRD2+), U9.1 (D1+), U9.10; also elsewhere on the board
ETH_D3_N: J4.10 (TRD3-), U9.5 (D2-), U9.6; also elsewhere on the board
ETH_D3_P: J4.9 (TRD3+), U9.4 (D2+), U9.7; also elsewhere on the board
ETH_nLED2: R22.1; also elsewhere on the board
ETH_nLED3: R23.1; also elsewhere on the board
GND: C30.2, C31.2, C32.2, C33.2, C34.2, C35.2, J2.1 (GND), J2.3 (GND), J2.9 (GND), J2.15 (GND), J2.21 (GND), J2.27 (GND), J2.33 (GND), J2.39 (GND), J2.45 (GND), J2.51 (GND), J2.57 (GND), J2.71 (GND), J2.73 (GND), J2.75 (GND), J3.10 (SHIELD), J3.A4 (GND), J3.A7 (DRAIN), J3.B4 (GND), J3.B7 (DRAIN), J4.19 (SHIELD), J4.20 (SHIELD), J5.A1 (GND), J5.A12 (GND), J5.B1 (GND), J5.B12 (GND), J5.SH (SHIELD), R21.2, R24.2, R25.2, U4.2 (GND), U8.3 (GND), U8.8 (GND), U9.3 (GND), U9.8 (GND), U10.2 (GND); also elsewhere on the board
PCIE_CLK_N: J2.53 (REFCLKn); also elsewhere on the board
PCIE_CLK_P: J2.55 (REFCLKp); also elsewhere on the board
PCIE_RX_N: J2.41 (PERn0/SATA-B+); also elsewhere on the board
PCIE_RX_P: J2.43 (PERp0/SATA-B-); also elsewhere on the board
PCIE_TX_N: J2.47 (PETn0/SATA-A-); also elsewhere on the board
PCIE_TX_P: J2.49 (PETp0/SATA-A+); also elsewhere on the board
PCIE_nCLKREQ: J2.52 (~CLKREQ); also elsewhere on the board
PCIE_nRST: J2.50 (~PERST); also elsewhere on the board
PCIE_nWAKE: J2.54 (~PEWAKE); also elsewhere on the board
USB2_N: J5.A7 (D-), J5.B7 (D-), U10.3 (I/O2), U10.4 (I/O2); also elsewhere on the board
USB2_P: J5.A6 (D+), J5.B6 (D+), U10.1 (I/O1), U10.6 (I/O1); also elsewhere on the board
USB3_0_DN: J3.B2 (D-); also elsewhere on the board
USB3_0_DP: J3.B3 (D+); also elsewhere on the board
USB3_0_RX_N: J3.B5 (SSRX-); also elsewhere on the board
USB3_0_RX_P: J3.B6 (SSRX+); also elsewhere on the board
USB3_0_TX_N: J3.B8 (SSTX-); also elsewhere on the board
USB3_0_TX_P: J3.B9 (SSTX+); also elsewhere on the board
USB3_1_DN: J3.A2 (D-); also elsewhere on the board
USB3_1_DP: J3.A3 (D+); also elsewhere on the board
VBUS_EN: U4.3 (EN); also elsewhere on the board
VBUS_USB: C32.1, C33.1, C34.1, J3.A1 (VBUS), J3.B1 (VBUS), U4.6 (OUT)

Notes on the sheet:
M.2 KEY-M NVMe (PCIe x1, 85 ohm diff)
USB HOST: 1x USB 3.0 + 1x USB 2.0 (90 ohm diff)
GIGABIT ETHERNET (MagJack + ESD, 100 ohm diff)
USB-C SERVICE (USB 2.0 device)
VBUS: AP22653 switch, ILIM = 15k -> ~1.5 A shared; EN = CM5 VBUS_EN
CM5 provides TX AC-coupling caps; NVMe module provides RX caps
rpiboot flashing / USB gadget console; CC = 5.1k Rd
USB-A ports carry no ESD array, matching the Raspberry Pi CM5 IO reference:
keeps the 5 Gb/s pair stub- and via-free (grounded shell + CM5 PHY protection).
Upper port: USB 3.0 (CM5 USB3-0). Lower port: USB 2.0 (CM5 USB3-1 D+/D-);
lower-port SuperSpeed contacts left open - routing trade-off, see docs.
